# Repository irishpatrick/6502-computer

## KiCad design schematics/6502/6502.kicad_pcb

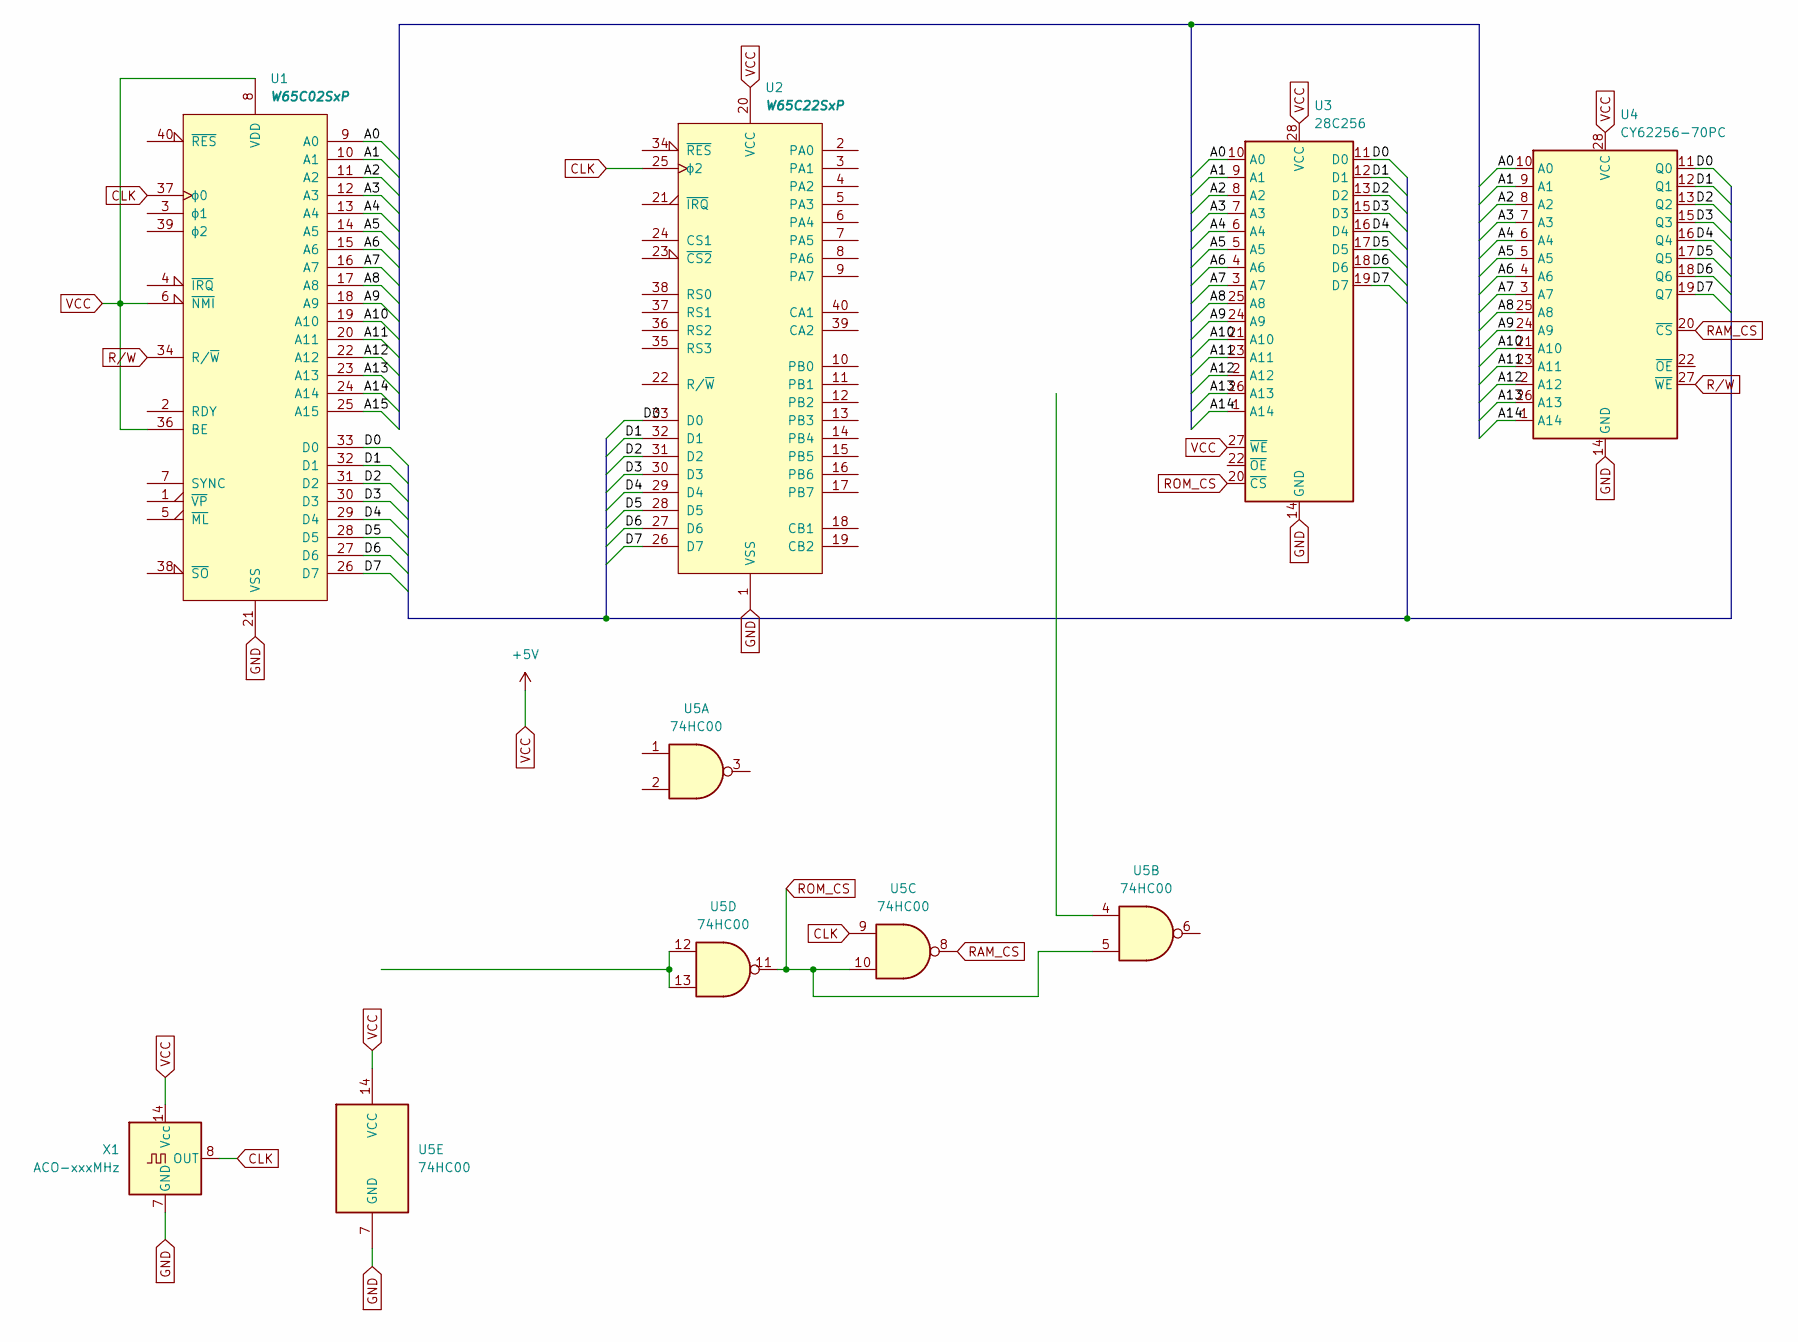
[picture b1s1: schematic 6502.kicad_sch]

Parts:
U1: W65C02SxP; DIP-40_W15.24mm_Socket
U2: W65C22SxP; DIP-40_W15.24mm_Socket
U3: 28C256; DIP-28_W15.24mm_Socket
U4: CY62256-70PC; DIP-28_W15.24mm
U5: 74HC00; DIP-14_W7.62mm_Socket
X1: ACO-xxxMHz; Oscillator_DIP-14

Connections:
/A0: U1.9 (A0), U3.10 (A0), U4.10 (A0)
/A1: U1.10 (A1), U3.9 (A1), U4.9 (A1)
/A2: U1.11 (A2), U3.8 (A2), U4.8 (A2)
/A3: U1.12 (A3), U3.7 (A3), U4.7 (A3)
/A4: U1.13 (A4), U3.6 (A4), U4.6 (A4)
/A5: U1.14 (A5), U3.5 (A5), U4.5 (A5)
/A6: U1.15 (A6), U3.4 (A6), U4.4 (A6)
/A7: U1.16 (A7), U3.3 (A7), U4.3 (A7)
/A8: U1.17 (A8), U3.25 (A8), U4.25 (A8)
/A9: U1.18 (A9), U3.24 (A9), U4.24 (A9)
/A10: U1.19 (A10), U3.21 (A10), U4.21 (A10)
/A11: U1.20 (A11), U3.23 (A11), U4.23 (A11)
/A12: U1.22 (A12), U3.2 (A12), U4.2 (A12)
/A13: U1.23 (A13), U3.26 (A13), U4.26 (A13)
/A14: U1.24 (A14), U3.1 (A14), U4.1 (A14)
/A15: U1.25 (A15)
/D0: U1.33 (D0), U2.33 (D0), U3.11 (D0), U4.11 (Q0)
/D1: U1.32 (D1), U2.32 (D1), U3.12 (D1), U4.12 (Q1)
/D2: U1.31 (D2), U2.31 (D2), U3.13 (D2), U4.13 (Q2)
/D3: U1.30 (D3), U2.30 (D3), U3.15 (D3), U4.15 (Q3)
/D4: U1.29 (D4), U2.29 (D4), U3.16 (D4), U4.16 (Q4)
/D5: U1.28 (D5), U2.28 (D5), U3.17 (D5), U4.17 (Q5)
/D6: U1.27 (D6), U2.27 (D6), U3.18 (D6), U4.18 (Q6)
/D7: U1.26 (D7), U2.26 (D7), U3.19 (D7), U4.19 (Q7)
CLK: U1.37 (ϕ0), U2.25 (ϕ2), U5.9, X1.8 (OUT)
GND: U1.21 (VSS), U2.1 (VSS), U3.14 (GND), U4.14 (GND), U5.7 (GND), X1.7 (GND)
unnamed: U5.12, U5.13
RAM_CS: U4.20 (~CS), U5.8
ROM_CS: U3.20 (~CS), U5.5, U5.10, U5.11
R/W: U1.34 (R/~W), U4.27 (~WE)
VCC: U1.6 (~NMI), U1.8 (VDD), U1.36 (BE), U2.20 (VCC), U3.27 (~WE), U3.28 (VCC), U4.28 (VCC), U5.14 (VCC), X1.14 (Vcc)

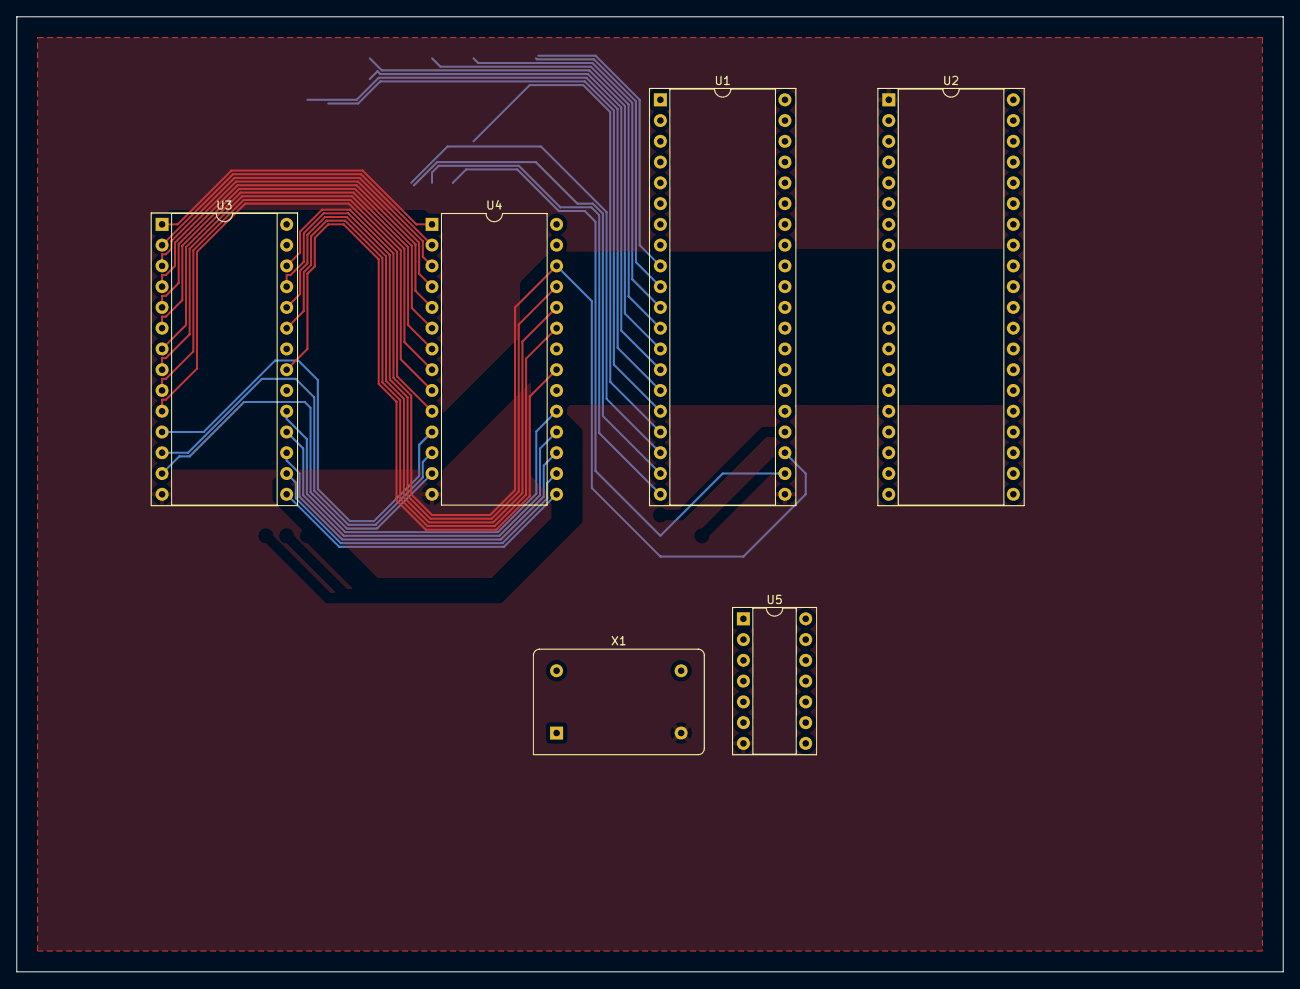
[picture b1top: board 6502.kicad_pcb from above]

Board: 2 copper layers, 154.9 x 116.8 mm, 6 parts (0 on the bottom side), 30 nets.

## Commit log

2022-02-23 add schematics
